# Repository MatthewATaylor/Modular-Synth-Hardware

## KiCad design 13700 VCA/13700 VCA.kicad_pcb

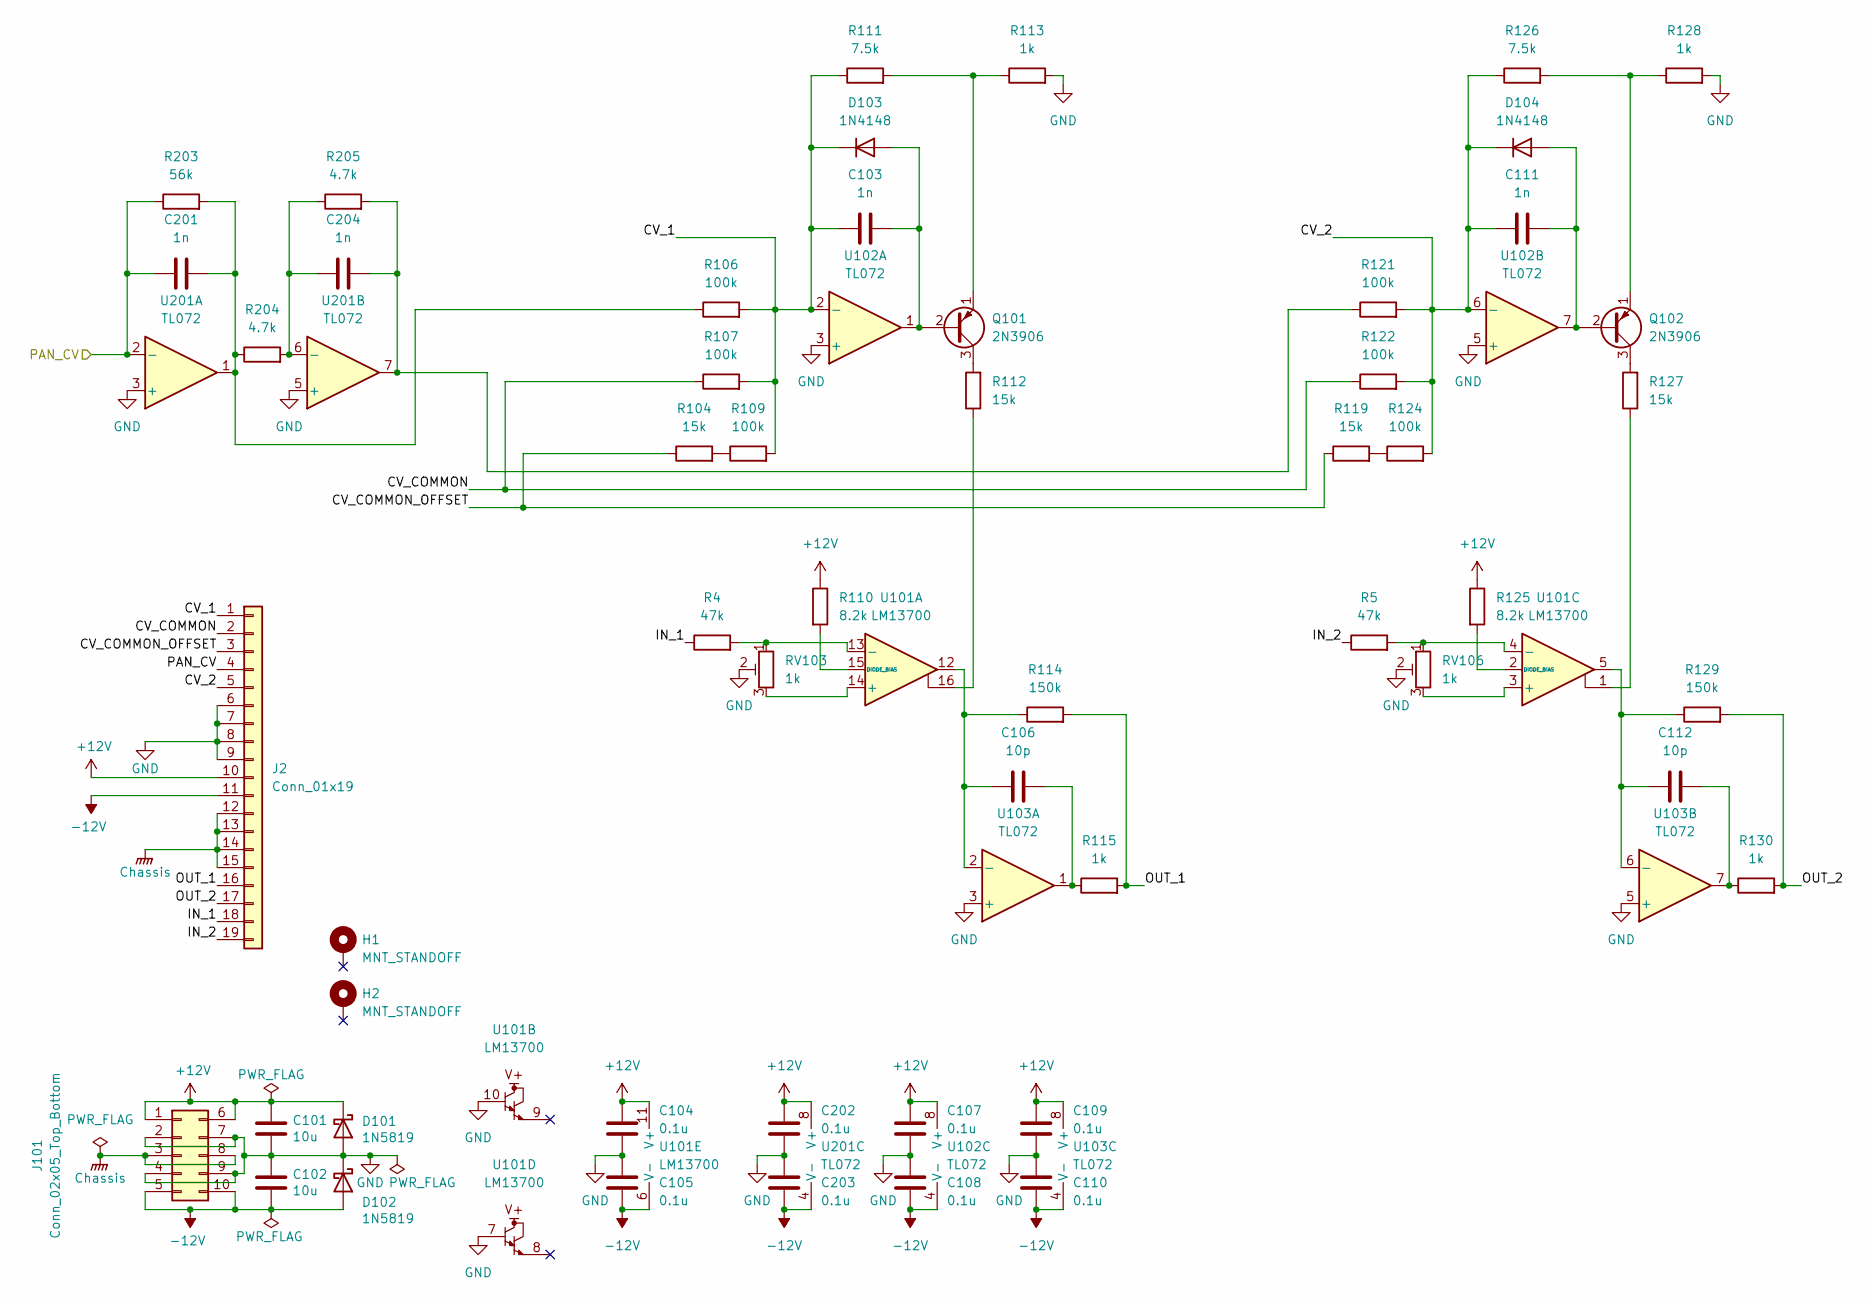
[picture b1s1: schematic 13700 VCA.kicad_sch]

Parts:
C101, C102: 10u; C_Disc_D5.5mm_W4.0mm_P2.50mm
C103, C111, C201, C204: 1n; C_Disc_D5.5mm_W2.5mm_P2.50mm
C104, C105, C107, C108, C109, C110, C202, C203: 0.1u; C_Disc_D5.5mm_W2.5mm_P2.50mm
C106, C112: 10p; C_Disc_D5.5mm_W2.5mm_P2.50mm
D101, D102: 1N5819; D_DO-41_SOD81_P10.16mm_Horizontal
D103, D104: 1N4148; D_DO-35_SOD27_P7.62mm_Horizontal
H1, H2: MNT_STANDOFF; MountingHole_Pitch7.5mm_Drill3.4mm
J2: Conn_01x19; PinHeader_1x19_P2.54mm_Vertical
J101: Conn_02x05_Top_Bottom; Molex_Mini-Fit_Jr_5566-10A_2x05_P4.20mm_Vertical
Q101, Q102: 2N3906; TO-92_HandSolder
R4, R5: 47k; R_Axial_DIN0207_L6.3mm_D2.5mm_P7.62mm_Horizontal
R104, R112, R119, R127: 15k; R_Axial_DIN0207_L6.3mm_D2.5mm_P7.62mm_Horizontal
R106, R107, R109, R121, R122, R124: 100k; R_Axial_DIN0207_L6.3mm_D2.5mm_P7.62mm_Horizontal
R110, R125: 8.2k; R_Axial_DIN0207_L6.3mm_D2.5mm_P7.62mm_Horizontal
R111, R126: 7.5k; R_Axial_DIN0207_L6.3mm_D2.5mm_P7.62mm_Horizontal
R113, R115, R128, R130: 1k; R_Axial_DIN0207_L6.3mm_D2.5mm_P7.62mm_Horizontal
R114, R129: 150k; R_Axial_DIN0207_L6.3mm_D2.5mm_P7.62mm_Horizontal
R203: 56k; R_Axial_DIN0207_L6.3mm_D2.5mm_P7.62mm_Horizontal
R204, R205: 4.7k; R_Axial_DIN0207_L6.3mm_D2.5mm_P7.62mm_Horizontal
RV103, RV106: 1k; Potentiometer_Bourns_3296W_Vertical
U101: LM13700; DIP-16_W7.62mm_Socket
U102, U103, U201: TL072; DIP-8_W7.62mm_Socket

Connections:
+12V: C101.1, C104.2, C107.2, C109.2, C202.2, D101.1 (K), J2.10, J101.1, J101.6, R110.1, R125.1, U101.11 (V+), U102.8 (V+), U103.8 (V+), U201.8 (V+)
-12V: C102.2, C105.1, C108.1, C110.1, C203.1, D102.2 (A), J2.11, J101.5, J101.10, U101.6 (V-), U102.4 (V-), U103.4 (V-), U201.4 (V-)
/CV_1: C103.1, D103.1 (K), J2.1, R106.2, R107.2, R109.2, R111.1, U102.2 (-)
/CV_2: C111.1, D104.1 (K), J2.5, R121.2, R122.2, R124.2, R126.1, U102.6 (-)
/CV_COMMON: J2.2, R107.1, R122.1
/CV_COMMON_OFFSET: J2.3, R104.1, R119.1
/IN_1: J2.18, R4.1
/IN_2: J2.19, R5.1
/OUT_1: J2.16, R114.2, R115.2
/OUT_2: J2.17, R129.2, R130.2
/PAN_CV: C201.1, J2.4, R203.1, U201.2 (-)
Chassis: J2.12, J2.13, J2.14, J2.15, J101.3, J101.8
GND: C101.2, C102.1, C104.1, C105.2, C107.1, C108.2, C109.1, C110.2, C202.1, C203.2, D101.2 (A), D102.1 (K), J2.6, J2.7, J2.8, J2.9, J101.2, J101.4, J101.7, J101.9, R113.2, R128.2, RV103.2, RV106.2, U101.7, U101.10, U102.3 (+), U102.5 (+), U103.3 (+), U103.5 (+), U201.3 (+), U201.5 (+)
unnamed: C106.2, R115.1, U103.1
unnamed: C112.2, R130.1, U103.7
unnamed: C201.2, R106.1, R203.2, R204.1, U201.1
unnamed: C204.2, R121.1, R205.2, U201.7
unnamed: C103.2, D103.2 (A), Q101.2 (B), U102.1
unnamed: C111.2, D104.2 (A), Q102.2 (B), U102.7
unnamed: Q101.3 (C), R112.2
unnamed: Q101.1 (E), R111.2, R113.1
unnamed: Q102.3 (C), R127.2
unnamed: Q102.1 (E), R126.2, R128.1
unnamed: R104.2, R109.1
unnamed: R112.1, U101.16
unnamed: R119.2, R124.1
unnamed: R127.1, U101.1
unnamed: RV103.3, U101.14 (+)
unnamed: R4.2, RV103.1, U101.13 (-)
unnamed: R110.2, U101.15 (DIODE_BIAS)
unnamed: RV106.3, U101.3 (+)
unnamed: R5.2, RV106.1, U101.4 (-)
unnamed: R125.2, U101.2 (DIODE_BIAS)
unnamed: C106.1, R114.1, U101.12, U103.2 (-)
unnamed: C112.1, R129.1, U101.5, U103.6 (-)
unnamed: C204.1, R204.2, R205.1, U201.6 (-)

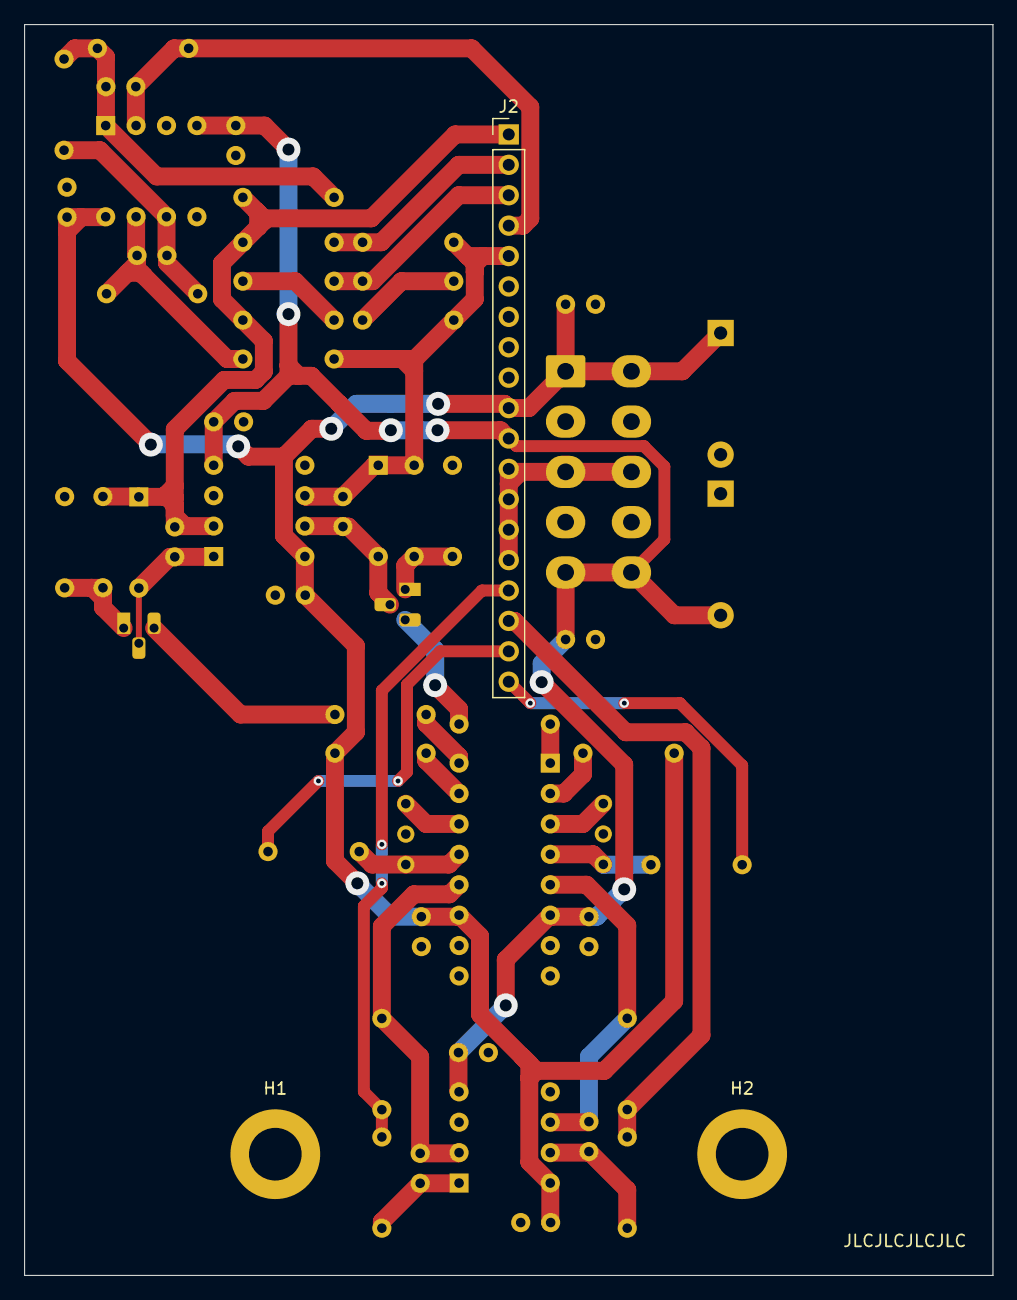
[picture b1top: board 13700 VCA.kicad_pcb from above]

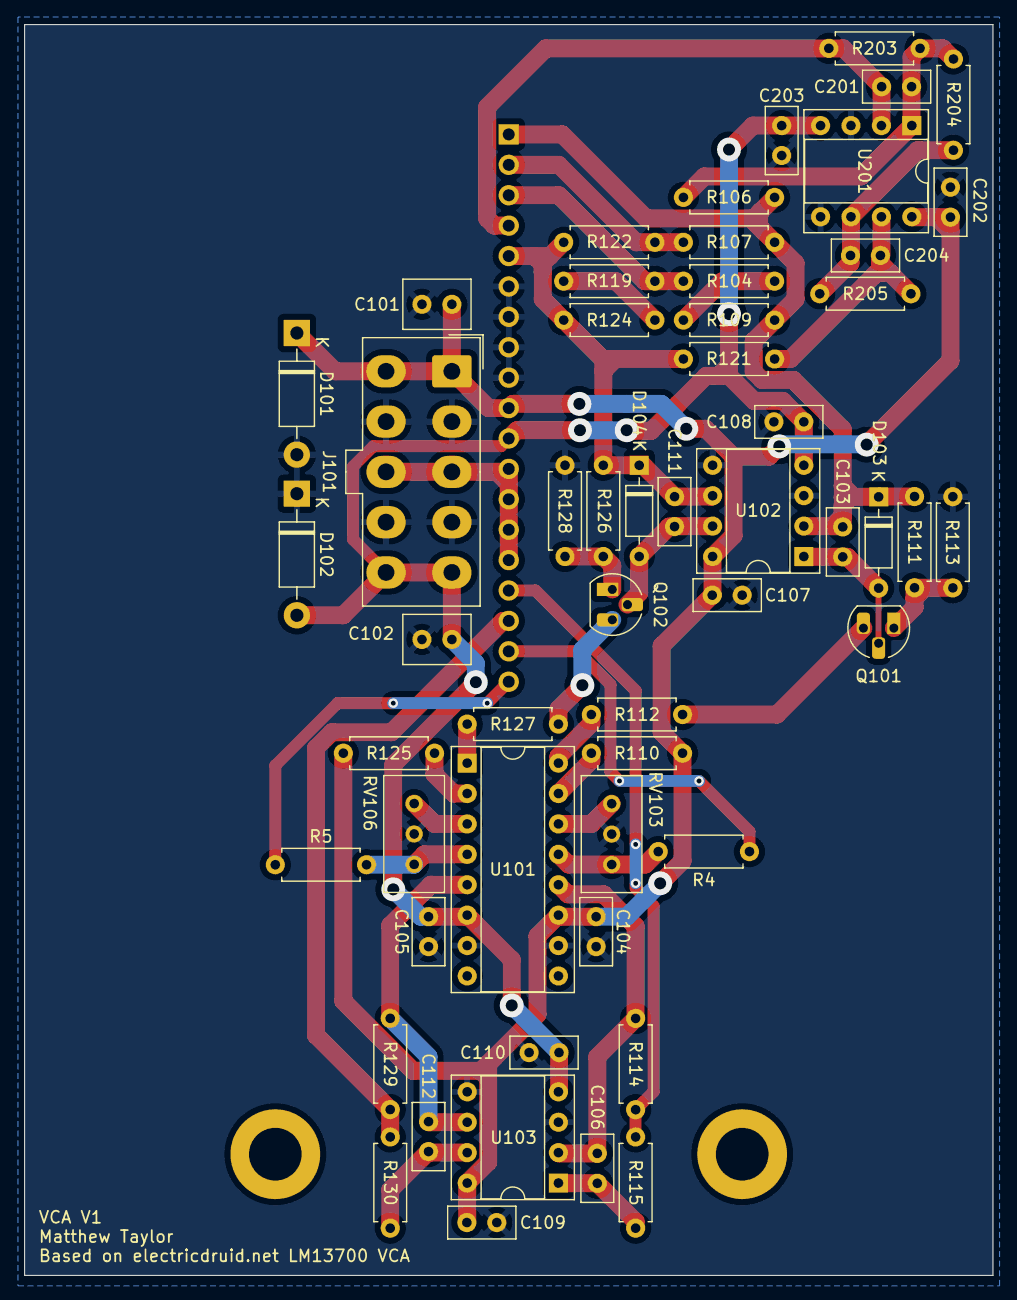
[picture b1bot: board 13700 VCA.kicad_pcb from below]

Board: 2 copper layers, 80.9 x 104.5 mm, 57 parts (54 on the bottom side), 36 nets.

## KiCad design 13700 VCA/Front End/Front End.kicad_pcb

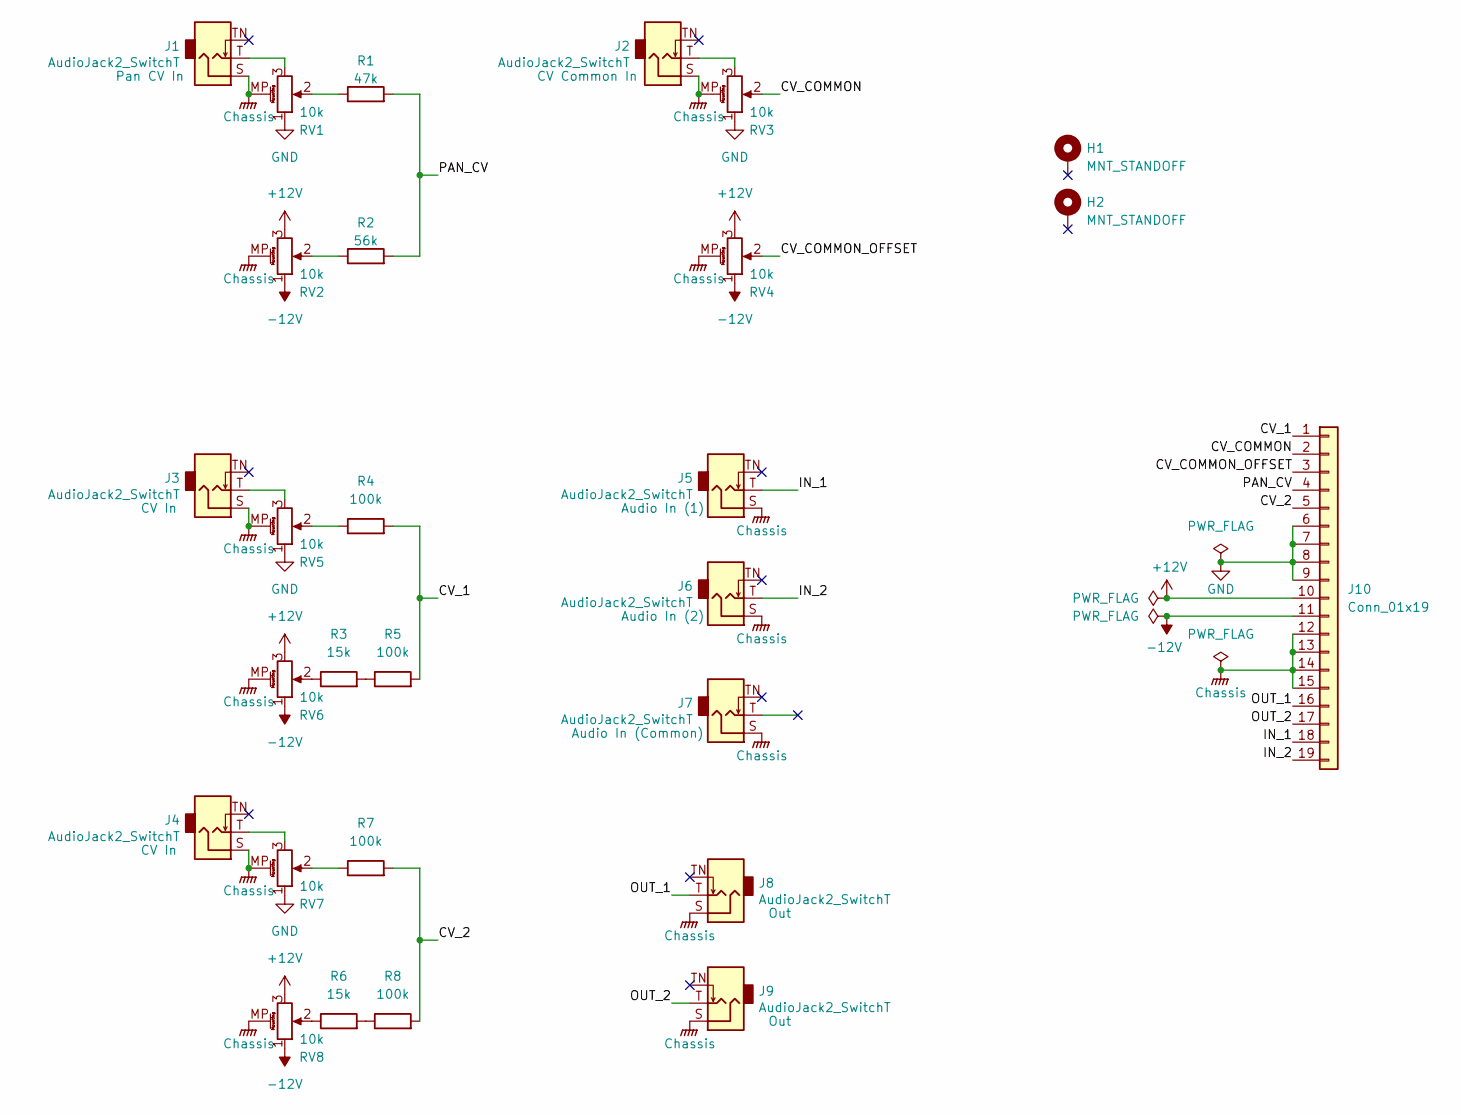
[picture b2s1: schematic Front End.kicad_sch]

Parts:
H1, H2: MNT_STANDOFF; MountingHole_Pitch7.5mm_Drill3.4mm
J1, J2, J3, J4, J5, J6, J7, J8, J9: AudioJack2_SwitchT; Jack_3.5mm_QingPu_WQP-PJ398SM_Vertical_CircularHoles
J10: Conn_01x19; PinHeader_1x19_P2.54mm_Vertical
R1: 47k; R_Axial_DIN0207_L6.3mm_D2.5mm_P7.62mm_Horizontal
R2: 56k; R_Axial_DIN0207_L6.3mm_D2.5mm_P7.62mm_Horizontal
R3, R6: 15k; R_Axial_DIN0207_L6.3mm_D2.5mm_P7.62mm_Horizontal
R4, R5, R7, R8: 100k; R_Axial_DIN0207_L6.3mm_D2.5mm_P7.62mm_Horizontal
RV1, RV2, RV3, RV4, RV5, RV6, RV7, RV8: 10k; Potentiometer_Alpha_RD901F-40-00D_Single_Vertical_MP

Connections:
+12V: J10.10, RV2.3, RV4.3, RV6.3, RV8.3
-12V: J10.11, RV2.1, RV4.1, RV6.1, RV8.1
/CV_1: J10.1, R4.2, R5.2
/CV_2: J10.5, R7.2, R8.2
/CV_COMMON: J10.2, RV3.2
/CV_COMMON_OFFSET: J10.3, RV4.2
/IN_1: J5.T, J10.18
/IN_2: J6.T, J10.19
/OUT_1: J8.T, J10.16
/OUT_2: J9.T, J10.17
/PAN_CV: J10.4, R1.2, R2.2
Chassis: J1.S, J2.S, J3.S, J4.S, J5.S, J6.S, J7.S, J8.S, J9.S, J10.12, J10.13, J10.14, J10.15, RV1.MP (MountPin), RV2.MP (MountPin), RV3.MP (MountPin), RV4.MP (MountPin), RV5.MP (MountPin), RV6.MP (MountPin), RV7.MP (MountPin), RV8.MP (MountPin)
GND: J10.6, J10.7, J10.8, J10.9, RV1.1, RV3.1, RV5.1, RV7.1
unnamed: J1.T, RV1.3
unnamed: J2.T, RV3.3
unnamed: J3.T, RV5.3
unnamed: J4.T, RV7.3
unnamed: R1.1, RV1.2
unnamed: R2.1, RV2.2
unnamed: R3.1, RV6.2
unnamed: R3.2, R5.1
unnamed: R4.1, RV5.2
unnamed: R6.1, RV8.2
unnamed: R6.2, R8.1
unnamed: R7.1, RV7.2

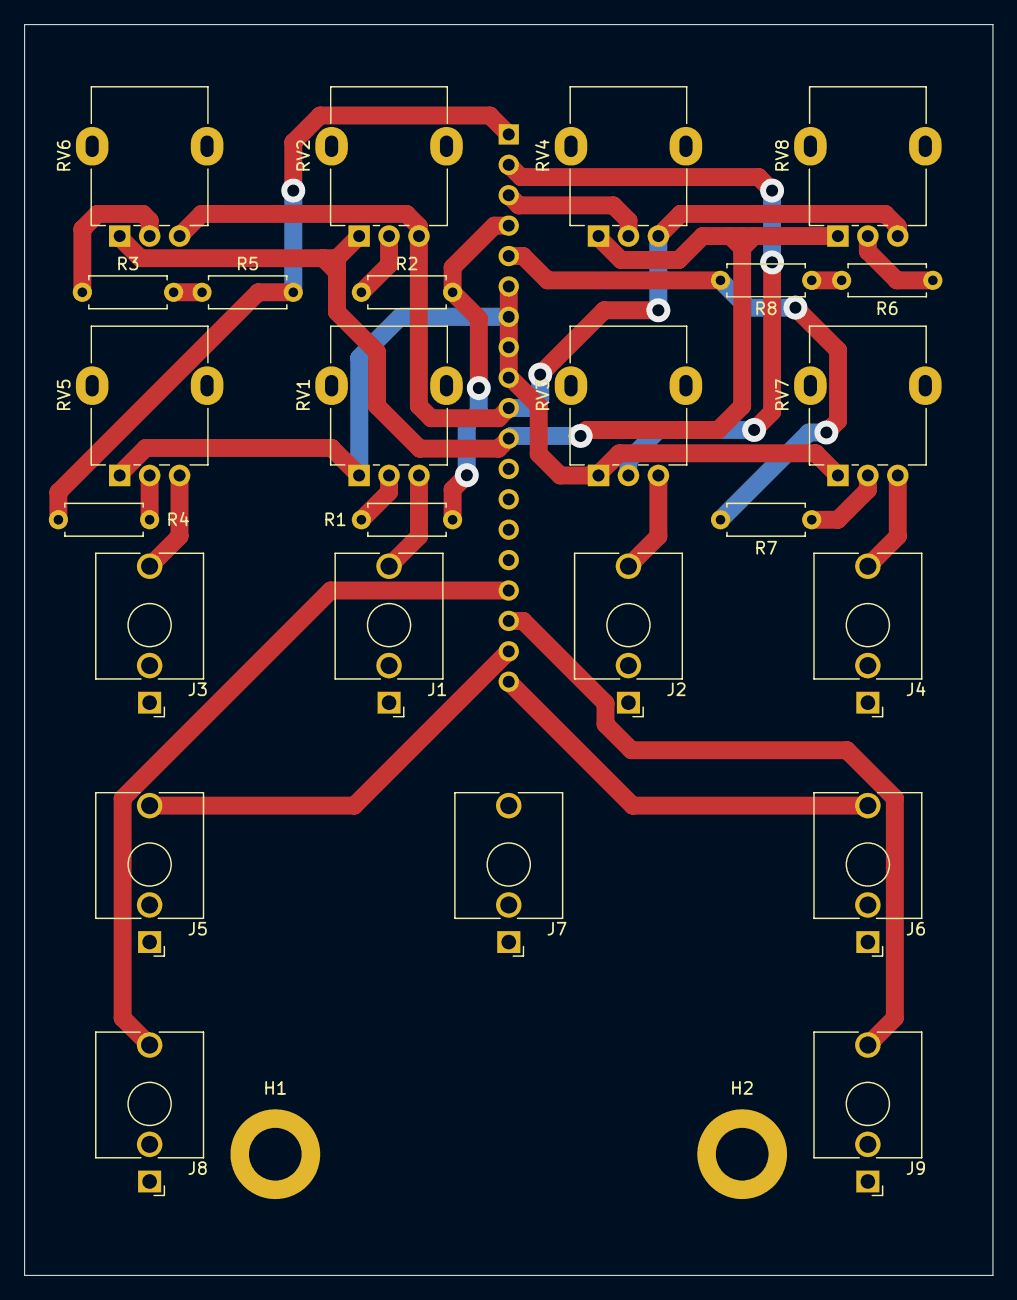
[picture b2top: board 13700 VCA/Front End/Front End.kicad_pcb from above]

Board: 2 copper layers, 80.9 x 104.5 mm, 28 parts (1 on the bottom side), 25 nets.

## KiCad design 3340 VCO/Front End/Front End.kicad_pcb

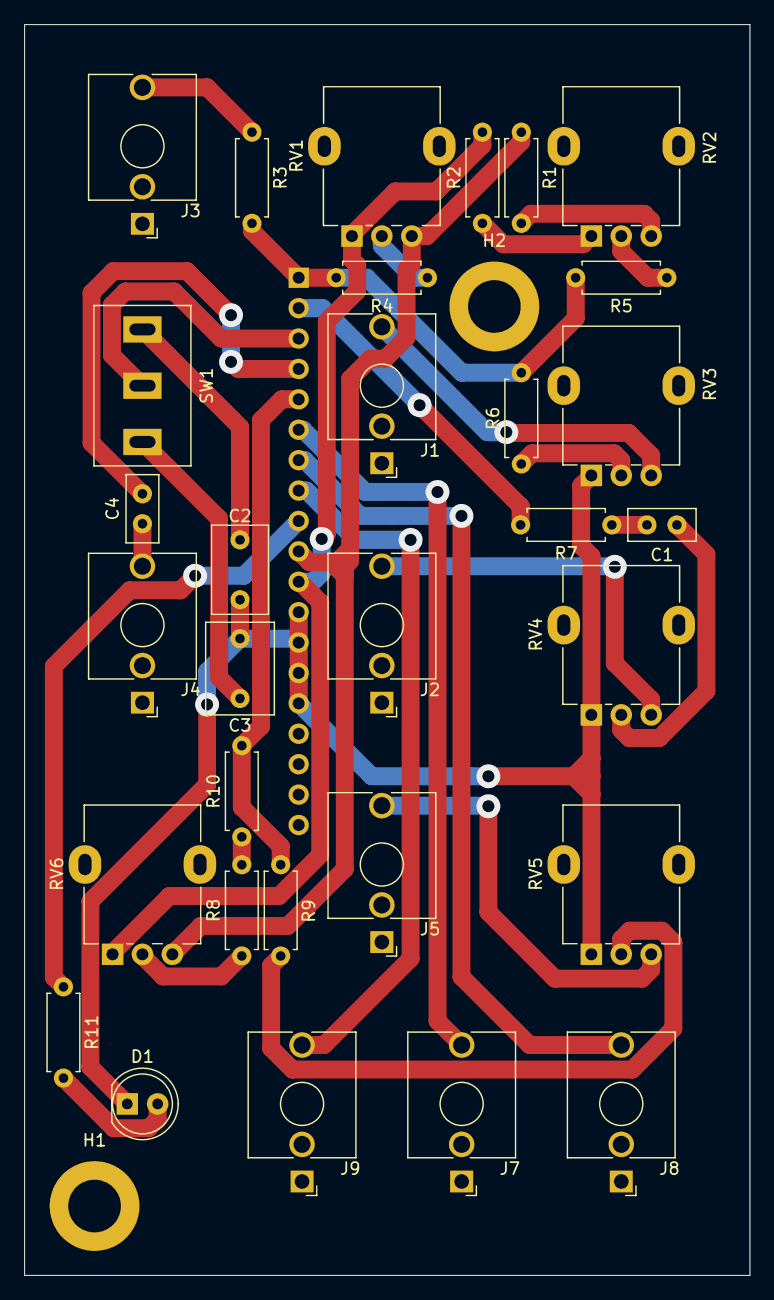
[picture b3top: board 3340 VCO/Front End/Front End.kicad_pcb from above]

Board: 2 copper layers, 60.6 x 104.5 mm, 34 parts (1 on the bottom side), 31 nets.

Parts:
C1: 0.1u; C_Disc_D5.5mm_W2.5mm_P2.50mm
C2: 1n; C_Rect_L7.2mm_W4.5mm_P5.00mm
C3: 10n; C_Rect_L7.5mm_W5.5mm_P5.00mm
C4: 1n; C_Disc_D5.5mm_W2.5mm_P2.50mm
D1: LED; LED_D5.0mm
H1, H2: MNT_STANDOFF; MountingHole_Pitch7.5mm_Drill3.4mm
J1, J2, J3, J4, J5, J7, J8, J9: AudioJack2_SwitchT; Jack_3.5mm_QingPu_WQP-PJ398SM_Vertical_CircularHoles
J6: Conn_01x19; PinHeader_1x19_P2.54mm_Vertical
R1, R2, R3, R4, R6, R9, R10: 100k; R_Axial_DIN0207_L6.3mm_D2.5mm_P7.62mm_Horizontal
R5: 220k; R_Axial_DIN0207_L6.3mm_D2.5mm_P7.62mm_Horizontal
R7: 1M; R_Axial_DIN0207_L6.3mm_D2.5mm_P7.62mm_Horizontal
R8: 15k; R_Axial_DIN0207_L6.3mm_D2.5mm_P7.62mm_Horizontal
R11: 33k; R_Axial_DIN0207_L6.3mm_D2.5mm_P7.62mm_Horizontal
RV1, RV2, RV3, RV4, RV5, RV6: 10k; Potentiometer_Alpha_RD901F-40-00D_Single_Vertical_MP
SW1: SW_SPDT; MTS-102_MTS-103_MTS-112_MTS-113_MTS-123

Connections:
+12V: J6.10, R1.1, RV1.3, RV6.3
-12V: J6.11, R2.2, RV1.1, RV6.1
/CAP: J6.3, SW1.2 (B)
/CV: J6.1, R3.2, R4.2, R5.2, R6.2
/FM_LIN: J6.2, R7.2
/HS: C4.2, J6.4
/LED: J6.9, R11.1
/PULSE: J6.6, J7.T
/PWM: J6.5, R9.2, R10.2
/RAMP: J6.7, J8.T
/TRI: J6.8, J9.T
Chassis: J1.S, J2.S, J3.S, J4.S, J5.S, J6.16, J6.17, J6.18, J6.19, J7.S, J8.S, J9.S, RV1.MP (MountPin), RV2.MP (MountPin), RV3.MP (MountPin), RV4.MP (MountPin), RV5.MP (MountPin), RV6.MP (MountPin)
GND: C2.1, C3.1, D1.1 (K), J6.12, J6.13, J6.14, J6.15, RV3.1, RV4.1, RV5.1
unnamed: C1.1, RV4.2
unnamed: C1.2, R7.1
unnamed: C4.1, J4.T
unnamed: D1.2 (A), R11.2
unnamed: J1.T, RV3.3
unnamed: J2.T, RV4.3
unnamed: J3.T, R3.1
unnamed: J5.T, RV5.3
unnamed: R1.2, RV2.3
unnamed: R2.1, RV2.1
unnamed: R4.1, RV1.2
unnamed: R5.1, RV2.2
unnamed: R6.1, RV3.2
unnamed: R8.1, RV6.2
unnamed: R9.1, RV5.2
unnamed: R8.2, R10.1
unnamed: C3.2, SW1.1 (A)
unnamed: C2.2, SW1.3 (C)

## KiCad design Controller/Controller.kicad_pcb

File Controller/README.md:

# Controller

An 8 voice MIDI to CV and 16-step sequencer module controlled by a Raspberry Pi (see code [here](https://github.com/MatthewATaylor/Modular-Synth-Software)).

### Note: Schematic Errors

* All buttons should be connected to 3V3 rather than 5V
* ADC input must go through a voltage divider to better fit within its input range

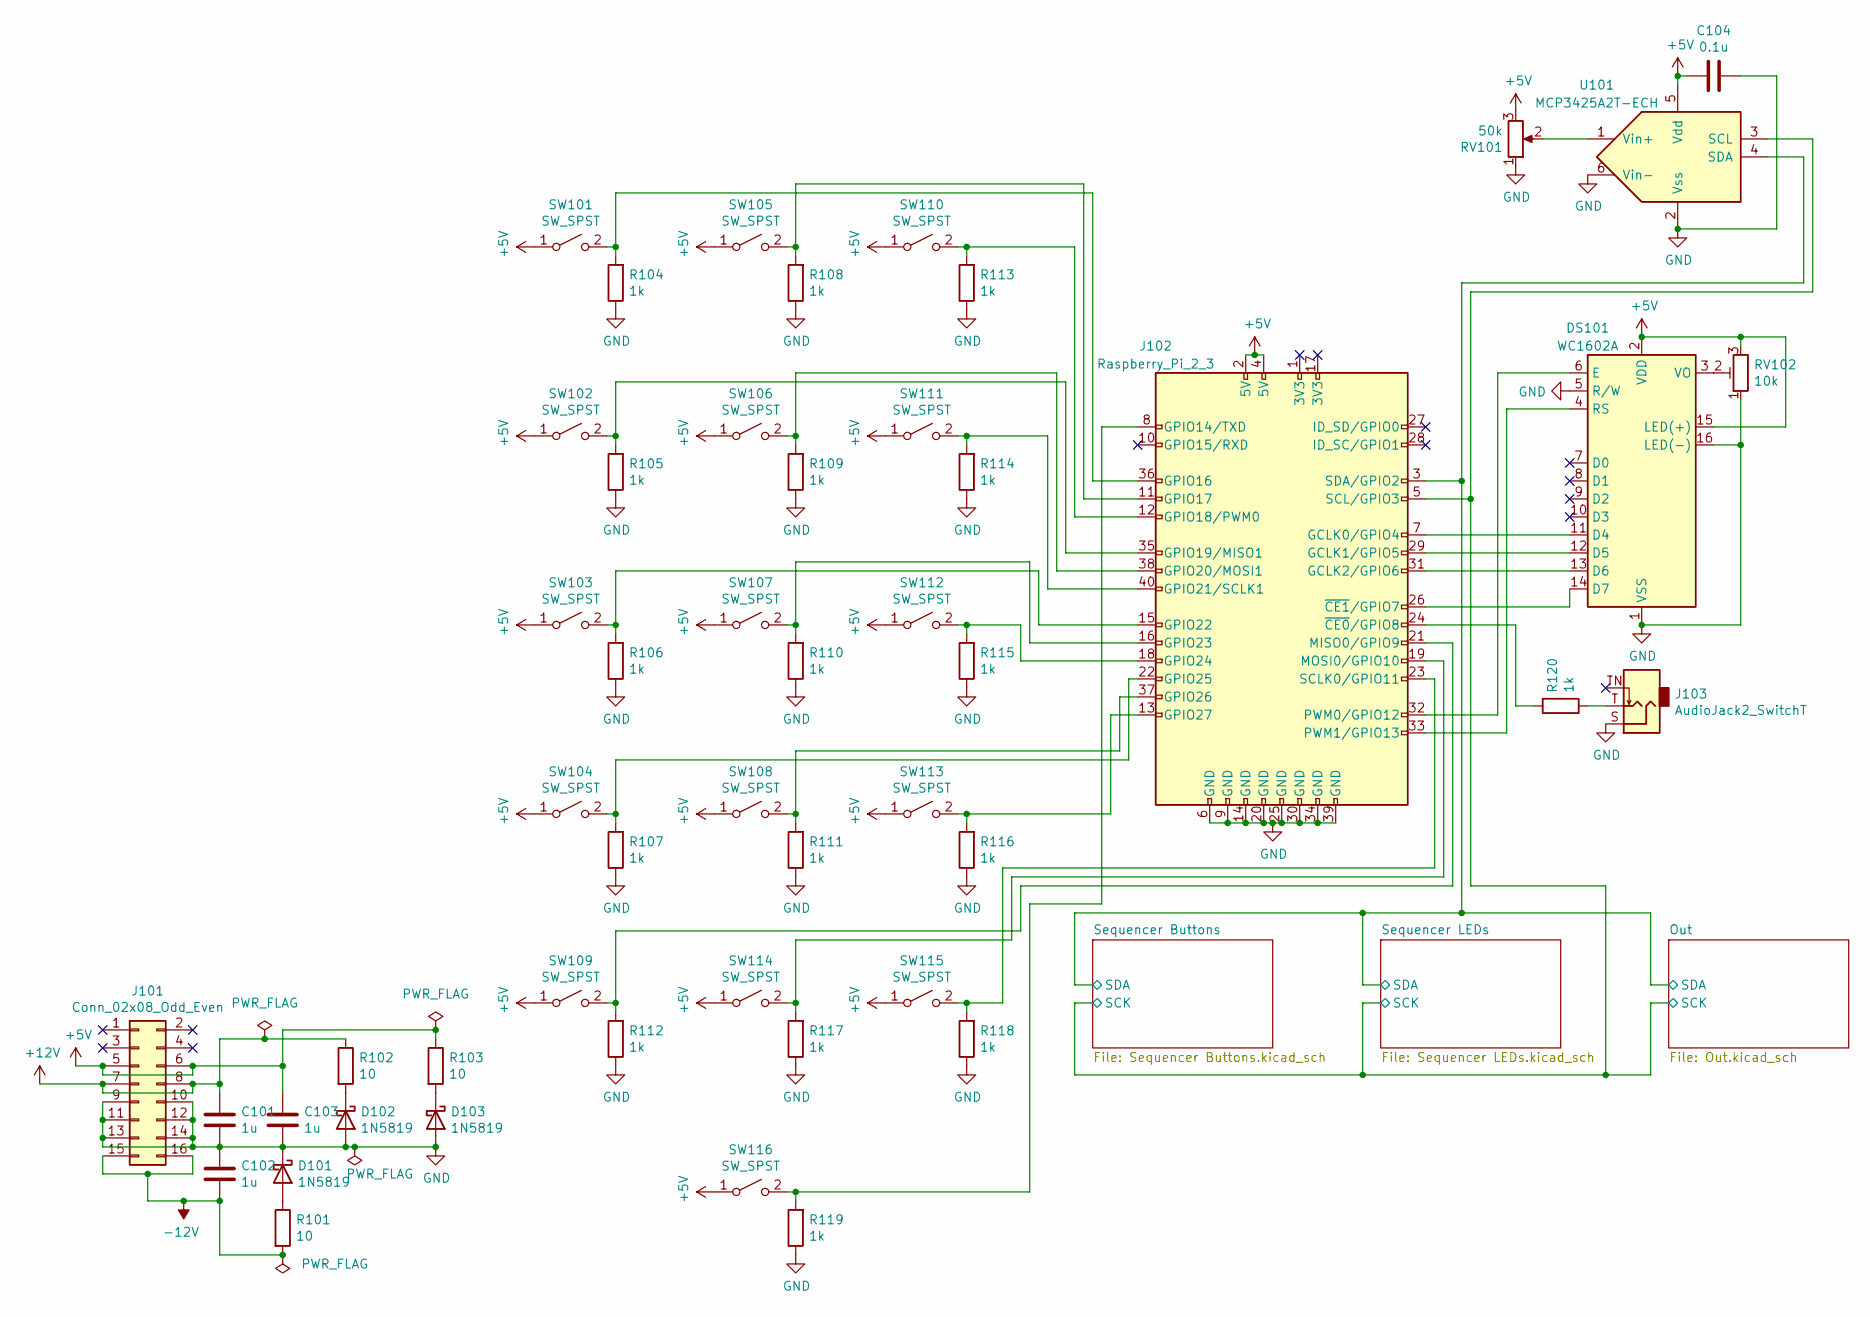
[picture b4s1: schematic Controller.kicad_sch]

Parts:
C101, C102, C103: 1u; C_Disc_D5.0mm_W2.5mm_P5.00mm
C104: 0.1u; C_Disc_D5.0mm_W2.5mm_P5.00mm
D101, D102, D103: 1N5819; D_DO-41_SOD81_P10.16mm_Horizontal
DS101: WC1602A; WC1602A_Outline
J101: Conn_02x08_Odd_Even; PinHeader_2x08_P2.54mm_Vertical
J102: Raspberry_Pi_2_3; Raspberry_Pi_Zero_Socketed_THT_FaceDown
J103: AudioJack2_SwitchT; Jack_3.5mm_QingPu_WQP-PJ398SM_Vertical_CircularHoles
R101, R102, R103: 10; R_Axial_DIN0207_L6.3mm_D2.5mm_P7.62mm_Horizontal
R104, R105, R106, R107, R108, R109, R110, R111, R112, R113, R114, R115, R116, R117, R118, R119, R120: 1k; R_Axial_DIN0207_L6.3mm_D2.5mm_P7.62mm_Horizontal
RV101: 50k; Potentiometer_Alpha_RD901F-40-00D_Single_Vertical_CircularH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
RV102: 10k; Potentiometer_Runtron_RM-065_Vertical
SW101, SW102, SW103, SW104, SW105, SW106, SW107, SW108, SW109, SW110, SW111, SW112, SW113, SW114, SW115, SW116: SW_SPST; PBS-105
U101: MCP3425A2T-ECH; SOT-23-6

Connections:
+5V: C103.1, C104.2, DS101.2 (VDD), DS101.15 (LED(+)), J101.5, J101.6, J102.2 (5V), J102.4 (5V), R103.1, RV101.3, RV102.3, SW101.1 (A), SW102.1 (A), SW103.1 (A), SW104.1 (A), SW105.1 (A), SW106.1 (A), SW107.1 (A), SW108.1 (A), SW109.1 (A), SW110.1 (A), SW111.1 (A), SW112.1 (A), SW113.1 (A), SW114.1 (A), SW115.1 (A), SW116.1 (A), U101.5 (Vdd); also elsewhere on the board
+12V: C101.1, J101.7, J101.8, R102.1
-12V: C102.2, J101.15, J101.16, R101.2
/Out/SCK: J102.5 (SCL/GPIO3), U101.3 (SCL); also elsewhere on the board
/Out/SDA: J102.3 (SDA/GPIO2), U101.4 (SDA); also elsewhere on the board
GND: C101.2, C102.1, C103.2, C104.1, D101.1 (K), D102.2 (A), D103.2 (A), DS101.1 (VSS), DS101.5 (R/W), DS101.16 (LED(-)), J101.9, J101.10, J101.11, J101.12, J101.13, J101.14, J102.6 (GND), J102.9 (GND), J102.14 (GND), J102.20 (GND), J102.25 (GND), J102.30 (GND), J102.34 (GND), J102.39 (GND), J103.S, R104.1, R105.1, R106.1, R107.1, R108.1, R109.1, R110.1, R111.1, R112.1, R113.1, R114.1, R115.1, R116.1, R117.1, R118.1, R119.1, RV101.1, RV102.1, U101.2 (Vss), U101.6 (Vin-); also elsewhere on the board
unnamed: D101.2 (A), R101.1
unnamed: D102.1 (K), R102.2
unnamed: D103.1 (K), R103.2
unnamed: DS101.3 (VO), RV102.2
unnamed: DS101.4 (RS), J102.33 (PWM1/GPIO13)
unnamed: DS101.6 (E), J102.32 (PWM0/GPIO12)
unnamed: DS101.11 (D4), J102.7 (GCLK0/GPIO4)
unnamed: DS101.12 (D5), J102.29 (GCLK1/GPIO5)
unnamed: DS101.13 (D6), J102.31 (GCLK2/GPIO6)
unnamed: DS101.14 (D7), J102.26 (~CE1/GPIO7)
unnamed: J102.8 (GPIO14/TXD), R119.2, SW116.2 (B)
unnamed: J102.11 (GPIO17), R108.2, SW105.2 (B)
unnamed: J102.12 (GPIO18/PWM0), R113.2, SW110.2 (B)
unnamed: J102.13 (GPIO27), R116.2, SW113.2 (B)
unnamed: J102.15 (GPIO22), R106.2, SW103.2 (B)
unnamed: J102.16 (GPIO23), R110.2, SW107.2 (B)
unnamed: J102.18 (GPIO24), R115.2, SW112.2 (B)
unnamed: J102.19 (MOSI0/GPIO10), R117.2, SW114.2 (B)
unnamed: J102.21 (MISO0/GPIO9), R112.2, SW109.2 (B)
unnamed: J102.22 (GPIO25), R107.2, SW104.2 (B)
unnamed: J102.23 (SCLK0/GPIO11), R118.2, SW115.2 (B)
unnamed: J102.24 (~CE0/GPIO8), R120.2
unnamed: J102.35 (GPIO19/MISO1), R105.2, SW102.2 (B)
unnamed: J102.36 (GPIO16), R104.2, SW101.2 (B)
unnamed: J102.37 (GPIO26), R111.2, SW108.2 (B)
unnamed: J102.38 (GPIO20/MOSI1), R109.2, SW106.2 (B)
unnamed: J102.40 (GPIO21/SCLK1), R114.2, SW111.2 (B)
unnamed: J103.T, R120.1
unnamed: RV101.2, U101.1 (Vin+)

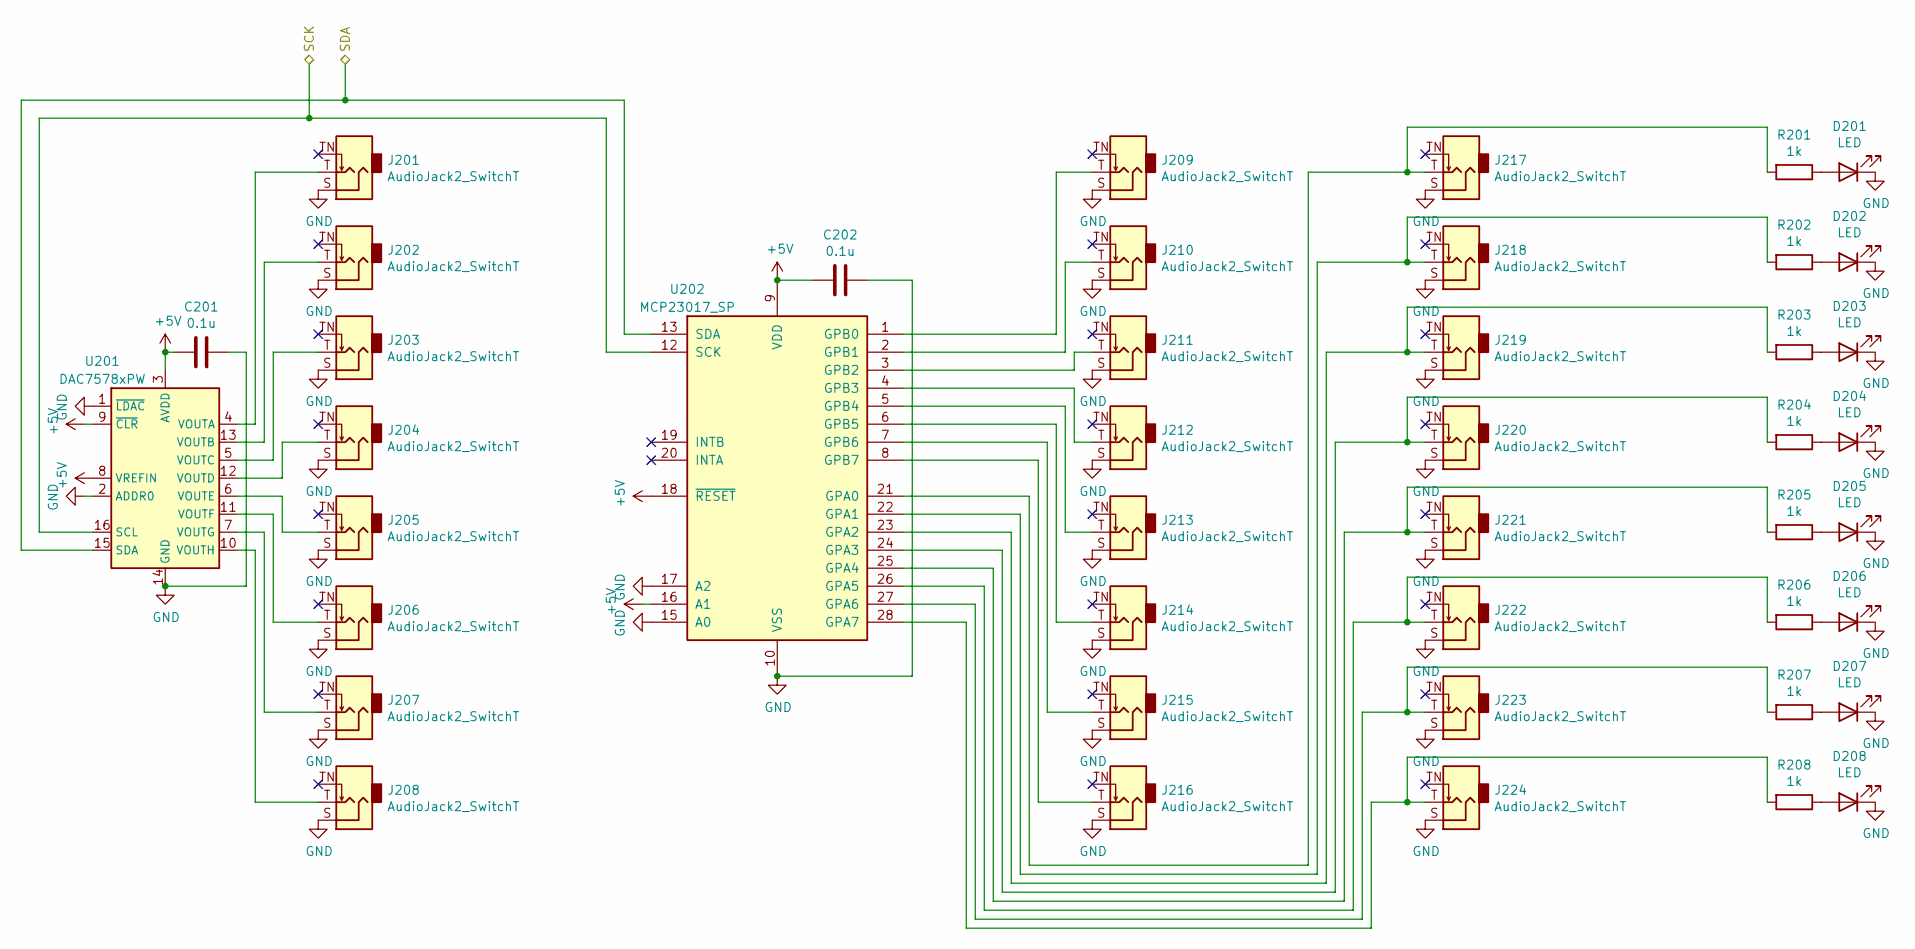
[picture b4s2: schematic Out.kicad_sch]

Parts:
C201, C202: 0.1u; C_Disc_D5.0mm_W2.5mm_P5.00mm
D201, D202, D203, D204, D205, D206, D207, D208: LED; LED_D5.0mm
J201, J202, J203, J204, J205, J206, J207, J208, J209, J210, J211, J212, J213, J214, J215, J216, J217, J218, J219, J220, J221, J222, J223, J224: AudioJack2_SwitchT; Jack_3.5mm_QingPu_WQP-PJ398SM_Vertical_CircularHoles
R201, R202, R203, R204, R205, R206, R207, R208: 1k; R_Axial_DIN0207_L6.3mm_D2.5mm_P7.62mm_Horizontal
U201: DAC7578xPW; TSSOP-16_4.4x5mm_P0.65mm
U202: MCP23017_SP; DIP-28_W7.62mm_Socket

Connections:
+5V: C201.2, C202.2, U201.3 (AVDD), U201.8 (VREFIN), U201.9 (~CLR), U202.9 (VDD), U202.16 (A1), U202.18 (~RESET); also elsewhere on the board
/Out/SCK: U201.16 (SCL), U202.12 (SCK); also elsewhere on the board
/Out/SDA: U201.15 (SDA), U202.13 (SDA); also elsewhere on the board
GND: C201.1, C202.1, D201.1 (K), D202.1 (K), D203.1 (K), D204.1 (K), D205.1 (K), D206.1 (K), D207.1 (K), D208.1 (K), J201.S, J202.S, J203.S, J204.S, J205.S, J206.S, J207.S, J208.S, J209.S, J210.S, J211.S, J212.S, J213.S, J214.S, J215.S, J216.S, J217.S, J218.S, J219.S, J220.S, J221.S, J222.S, J223.S, J224.S, U201.1 (~LDAC), U201.2 (ADDR0), U201.14 (GND), U202.10 (VSS), U202.15 (A0), U202.17 (A2); also elsewhere on the board
unnamed: D201.2 (A), R201.1
unnamed: D202.2 (A), R202.1
unnamed: D203.2 (A), R203.1
unnamed: D204.2 (A), R204.1
unnamed: D205.2 (A), R205.1
unnamed: D206.2 (A), R206.1
unnamed: D207.2 (A), R207.1
unnamed: D208.2 (A), R208.1
unnamed: J201.T, U201.4 (VOUTA)
unnamed: J202.T, U201.13 (VOUTB)
unnamed: J203.T, U201.5 (VOUTC)
unnamed: J204.T, U201.12 (VOUTD)
unnamed: J205.T, U201.6 (VOUTE)
unnamed: J206.T, U201.11 (VOUTF)
unnamed: J207.T, U201.7 (VOUTG)
unnamed: J208.T, U201.10 (VOUTH)
unnamed: J209.T, U202.1 (GPB0)
unnamed: J210.T, U202.2 (GPB1)
unnamed: J211.T, U202.3 (GPB2)
unnamed: J212.T, U202.4 (GPB3)
unnamed: J213.T, U202.5 (GPB4)
unnamed: J214.T, U202.6 (GPB5)
unnamed: J215.T, U202.7 (GPB6)
unnamed: J216.T, U202.8 (GPB7)
unnamed: J217.T, R201.2, U202.21 (GPA0)
unnamed: J218.T, R202.2, U202.22 (GPA1)
unnamed: J219.T, R203.2, U202.23 (GPA2)
unnamed: J220.T, R204.2, U202.24 (GPA3)
unnamed: J221.T, R205.2, U202.25 (GPA4)
unnamed: J222.T, R206.2, U202.26 (GPA5)
unnamed: J223.T, R207.2, U202.27 (GPA6)
unnamed: J224.T, R208.2, U202.28 (GPA7)

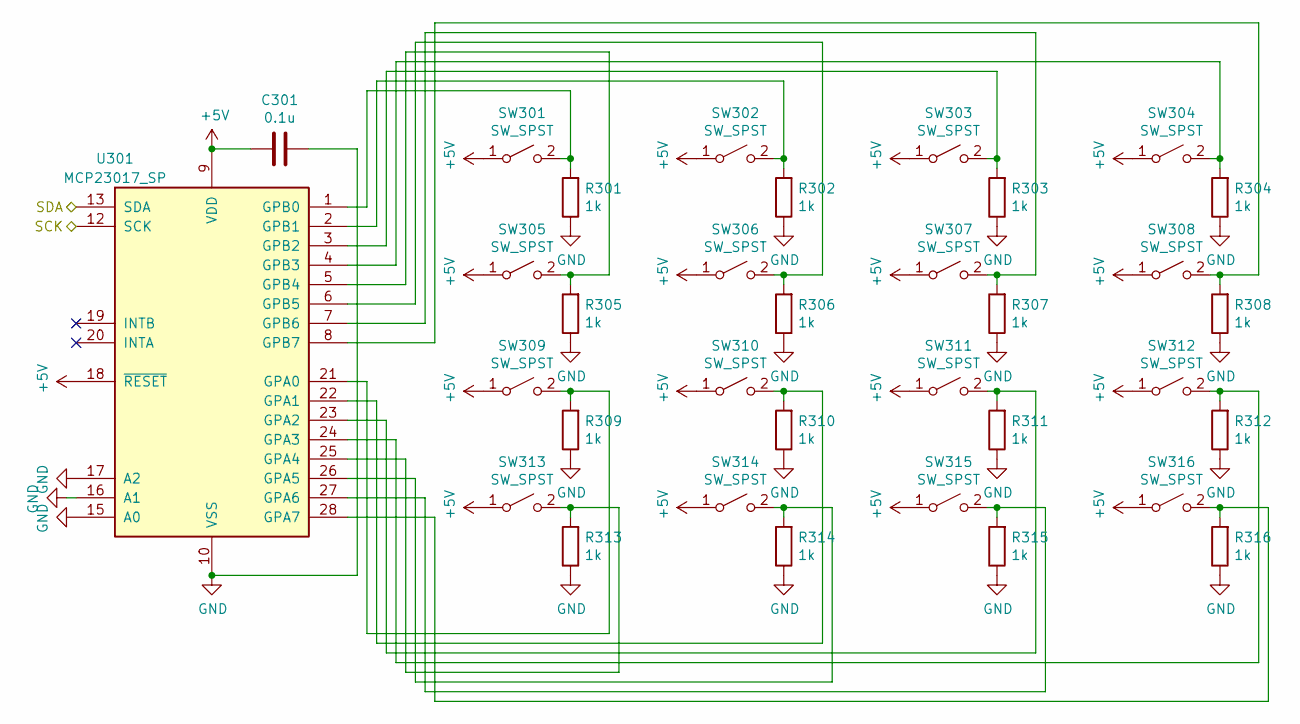
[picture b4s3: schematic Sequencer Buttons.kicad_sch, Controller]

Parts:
C301: 0.1u; C_Disc_D5.0mm_W2.5mm_P5.00mm
R301, R302, R303, R304, R305, R306, R307, R308, R309, R310, R311, R312, R313, R314, R315, R316: 1k; R_Axial_DIN0207_L6.3mm_D2.5mm_P7.62mm_Horizontal
SW301, SW302, SW303, SW304, SW305, SW306, SW307, SW308, SW309, SW310, SW311, SW312, SW313, SW314, SW315, SW316: SW_SPST; PBS-105
U301: MCP23017_SP; DIP-28_W7.62mm_Socket

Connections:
+5V: C301.2, SW301.1 (A), SW302.1 (A), SW303.1 (A), SW304.1 (A), SW305.1 (A), SW306.1 (A), SW307.1 (A), SW308.1 (A), SW309.1 (A), SW310.1 (A), SW311.1 (A), SW312.1 (A), SW313.1 (A), SW314.1 (A), SW315.1 (A), SW316.1 (A), U301.9 (VDD), U301.18 (~RESET); also elsewhere on the board
/Out/SCK: U301.12 (SCK); also elsewhere on the board
/Out/SDA: U301.13 (SDA); also elsewhere on the board
GND: C301.1, R301.1, R302.1, R303.1, R304.1, R305.1, R306.1, R307.1, R308.1, R309.1, R310.1, R311.1, R312.1, R313.1, R314.1, R315.1, R316.1, U301.10 (VSS), U301.15 (A0), U301.16 (A1), U301.17 (A2); also elsewhere on the board
unnamed: R301.2, SW301.2 (B), U301.1 (GPB0)
unnamed: R302.2, SW302.2 (B), U301.2 (GPB1)
unnamed: R303.2, SW303.2 (B), U301.3 (GPB2)
unnamed: R304.2, SW304.2 (B), U301.4 (GPB3)
unnamed: R305.2, SW305.2 (B), U301.5 (GPB4)
unnamed: R306.2, SW306.2 (B), U301.6 (GPB5)
unnamed: R307.2, SW307.2 (B), U301.7 (GPB6)
unnamed: R308.2, SW308.2 (B), U301.8 (GPB7)
unnamed: R309.2, SW309.2 (B), U301.21 (GPA0)
unnamed: R310.2, SW310.2 (B), U301.22 (GPA1)
unnamed: R311.2, SW311.2 (B), U301.23 (GPA2)
unnamed: R312.2, SW312.2 (B), U301.24 (GPA3)
unnamed: R313.2, SW313.2 (B), U301.25 (GPA4)
unnamed: R314.2, SW314.2 (B), U301.26 (GPA5)
unnamed: R315.2, SW315.2 (B), U301.27 (GPA6)
unnamed: R316.2, SW316.2 (B), U301.28 (GPA7)
